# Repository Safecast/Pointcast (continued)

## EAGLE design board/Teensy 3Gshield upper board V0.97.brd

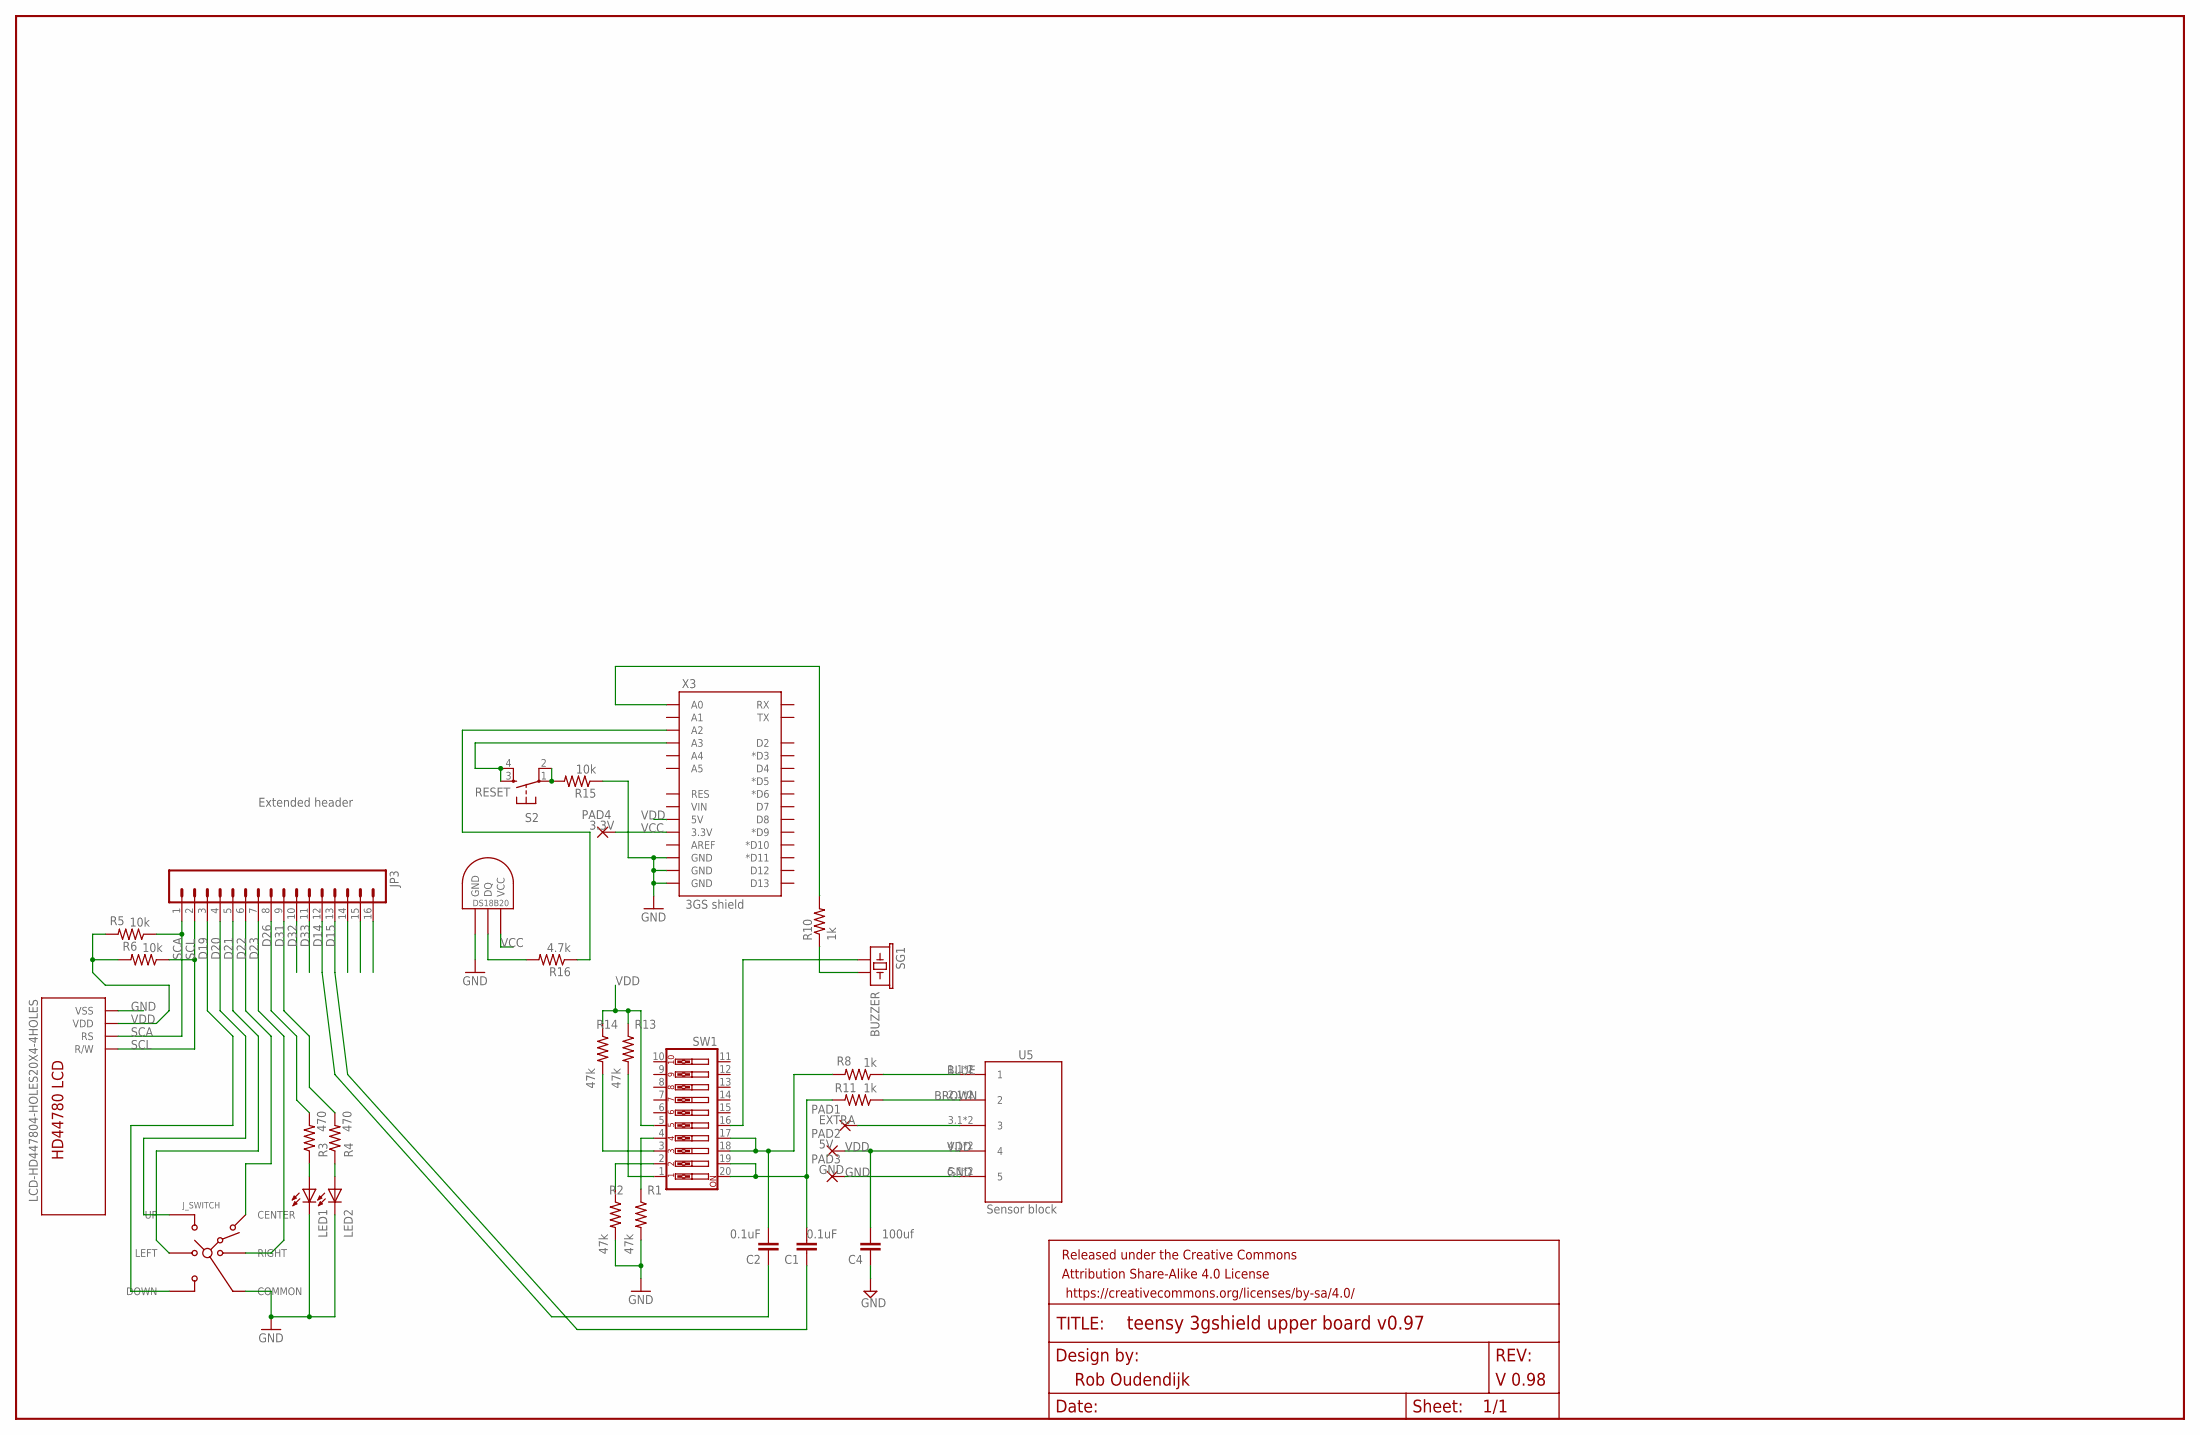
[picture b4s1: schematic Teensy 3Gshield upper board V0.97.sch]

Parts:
C1, C2: 0.1uF; CAP-PTH-SMALL-KIT
C4: 100uf; C025-024X044
FRAME1: FRAME-LEDGER; CREATIVE_COMMONS
JP3: Extended header; 1X16
J_SWITCH: SKQUCAA010; SKQU
LED1, LED2: LED5MM
PAD1: EXTRA; 2,15/1,0
PAD2: 5V; 2,15/1,0
PAD3: GND; 2,15/1,0
PAD4: 3.3V; 2,15/1,0
R1, R2, R13, R14: 47k; AXIAL-0.3
R3, R4: 470; AXIAL-0.3EZ
R5, R6: 10k; AXIAL-0.3
R8, R11: 1k; AXIAL-0.3
R10: 1k; AXIAL-0.3EZ
R15: 10k; AXIAL-0.3EZ
R16: 4.7k; AXIAL-0.3EZ
S2: RESET; DTS-6
SG1: BUZZER; BUZZER-12MM
SW1: SW_DIP-10; EDG-10
U5: Sensor block; SREWLESS_TERMINATOR_5PIN
U$2: DS1820TO92; DS1820
X1: LCD-HD447804-HOLES20X4-4HOLES; LCD-20X4-4HOLES
X3: 3GS shield; DUEMILANOVE_SHIELD

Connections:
BLUE: R8.P$1 (1), U5.1.1 (1), U5.1.2 (1)
BROWN: R11.P$1 (1), U5.2.1 (2), U5.2.2 (2)
D14: JP3.12
D15: JP3.13
D19: JP3.3, J_SWITCH.DOWN
D20: JP3.4, J_SWITCH.UP
D21: JP3.5, J_SWITCH.LEFT
D22: JP3.6, J_SWITCH.CENTER
D23: JP3.7, J_SWITCH.RIGHT
D26: JP3.8, R3.P$2 (2)
D31: JP3.9, R4.P$2 (2)
D32: JP3.10
D33: JP3.11
GND: C4.1, J_SWITCH.COMMON, LED1.K (C), LED2.K (C), PAD3.1, R1.P$2 (2), R2.P$2 (2), R15.P$1 (1), U5.5.1 (5), U5.5.2 (5), U$2.GND, X1.P$13 (VSS), X3.GND@0 (GND), X3.GND@1 (GND), X3.GND@2 (GND)
unnamed: SG1.+ (1), SW1.16
unnamed: LED1.A, R3.P$1 (1)
unnamed: R10.P$2 (2), X3.A0
unnamed: R14.P$2 (2), SW1.3
unnamed: R10.P$1 (1), SG1.- (2)
unnamed: R16.P$2 (2), U$2.DQ
unnamed: C1.2, R11.P$2 (2), SW1.19, SW1.20
unnamed: R16.P$1 (1), X3.A2
unnamed: R13.P$2 (2), SW1.1
unnamed: LED2.A, R4.P$1 (1)
unnamed: R15.P$2 (2), S2.1, S2.2
unnamed: S2.3, S2.4, X3.A3
unnamed: C2.2, R8.P$2 (2), SW1.17, SW1.18
unnamed: PAD1.1, U5.3.1 (3), U5.3.2 (3)
SCA: JP3.1, R5.P$1 (1), X1.P$15 (RS)
SCL: JP3.2, R6.P$1 (1), X1.P$16 (R/W)
VCC: PAD4.1, U$2.VDD (VCC), X3.3.3V
VDD: C4.2, PAD2.1, R5.P$2 (2), R6.P$2 (2), R13.P$1 (1), R14.P$1 (1), SW1.5, U5.4.1 (4), U5.4.2 (4), X1.P$14 (VDD), X3.5V
VDD1: R1.P$1 (1), R2.P$1 (1), SW1.2, SW1.4

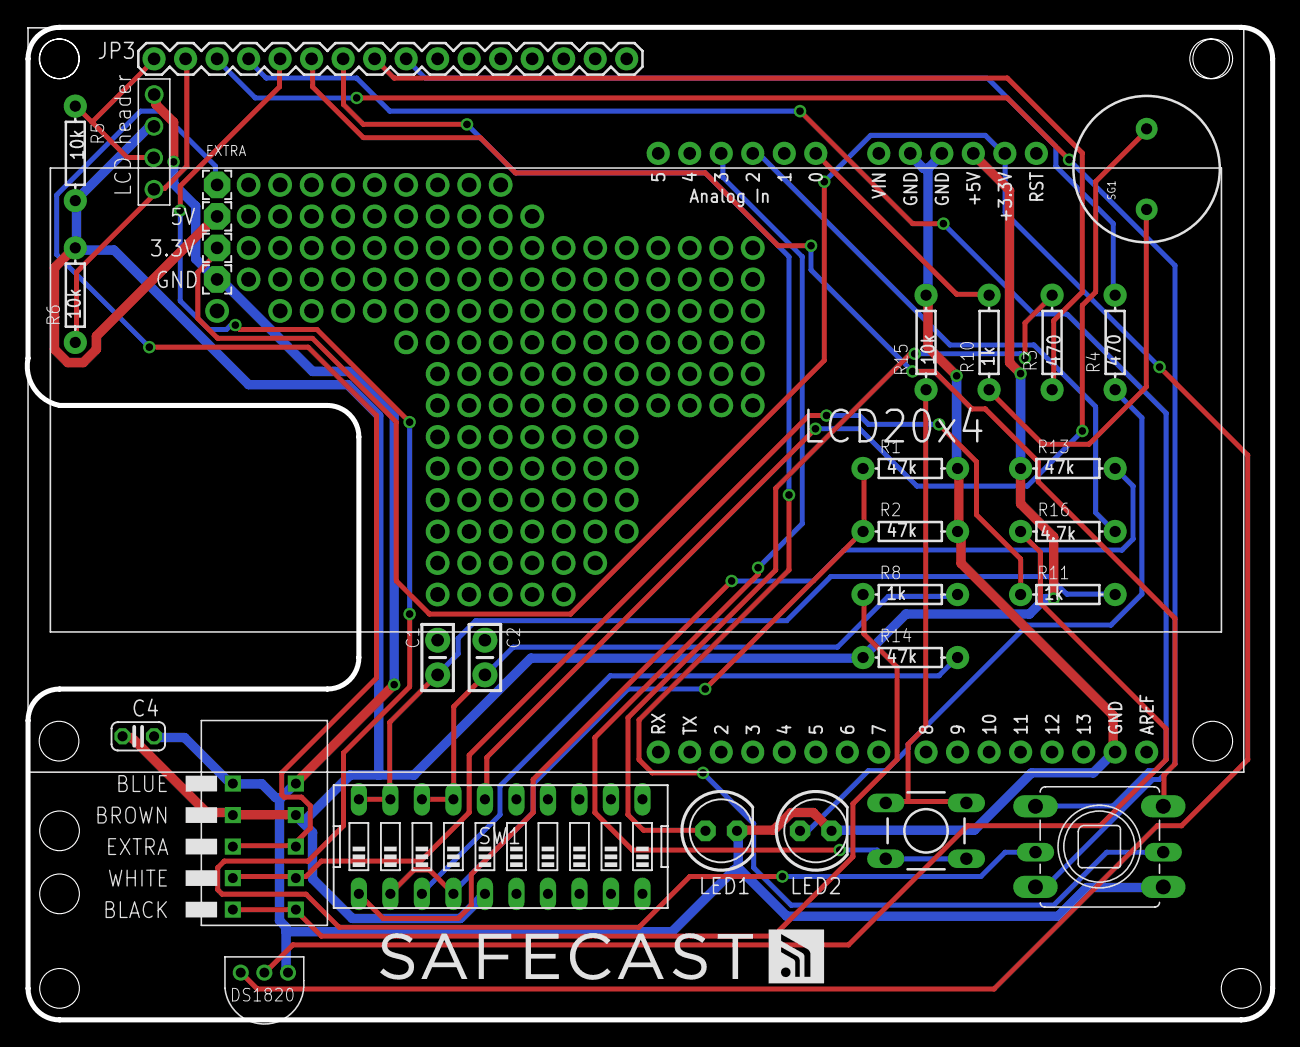
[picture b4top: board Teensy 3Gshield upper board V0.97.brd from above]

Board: 2 copper layers, 100.4 x 80.0 mm, 33 parts (0 on the bottom side), 29 nets.

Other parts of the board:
U$10: SAFECAST_LOGO1

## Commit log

2015-02-28 initial project version
2015-03-03 Fixed dual upload and interupt routine deleted displaying pulses.
2015-03-03 Added zipped hex file
2015-03-03 Changed time for sending to 5 minutes.
2015-03-03 Version change
2015-03-03 And the compressed hex file
2015-03-03 Changed display messages
2015-03-03 layout of display changed
2015-03-05 Pull up active on inputs inputs are setup for falling edge
2015-03-07 Added upldated Hex file
2015-03-07 renamed Hex zip file
2015-03-09 Added libraries and new boards
2015-03-09 Added more files
2015-03-09 Update I2C library and added Hex file
2015-03-09 Added Gerber files
2015-03-09 Cleaned up code, added final boards.
2015-04-01 Create gh-pages branch via GitHub
2015-04-04 Added reset to A14
2015-04-05 Added LED check on startup..
2015-04-06 LED delay setup
2015-04-07 Code for Ethetnet and 3G combined
2015-04-07 Send and recieve every 5 minutes. (2.6.1 was every 5 seconds for stress testing)
2015-04-09 Switch between DEV and API sending the data...
2015-04-13 added switch for switching from Ethernet and other options to switch in the coding without recompile.
2015-04-13 Added heart beat on green LED every 10 seconds..
2015-04-14 Switched back to two compile versions(3G and Ethernet) and added setup variables
2015-04-14 Added extra setup files
2015-04-21 V2.6.8 added device ID, startup screen change, header for file format changed to NGRDD
2015-04-23 Sensor header added as second line on SDcard
2015-04-27 Changed name repro
2015-04-27 changed name
2015-04-27 And all the other files updated to Pointcast
2015-04-27 More files
2015-04-27 Version named too..
2015-04-27 Added latest boards
2015-04-27 And the boards
2015-04-30 Added temperature setup for DS18B20 (disabled at the moment) setup screens
2015-05-02 V2.7.3 Added joystick setup functions, cleanup code
2015-05-04 Added height info
2015-05-04 Fixed lot/lan sending information on Ethernet
2015-05-07 V2.7.3 with SDCard files corrected..
2015-05-07 Display SDCard errors was disabled.. Now enbaled.
2015-05-08 V2.7.4 More screens and error reporting.
2015-05-10 Renaming and 3G display screen setup
2015-05-10 Added sdcard files
2015-05-14 BOM updated
2015-05-16 V2.7.9 Added Joystick interaction. Key down startup 1/5 of normal time. Prepare joy stick enter ket (push down) for other functions.
2015-05-16 Extra files added
2015-05-18 Automatic time setup on Ethernet NTP
2015-05-19 Fixes for 3G after RTC updates (RTC for 3G not setup yet)
2015-05-20 Added random auto gateway , added fast troubleshooting mode
2015-05-22 Added "trb=0" option to the sdcard setup be able to fast trouble shoot the senor
2015-05-24 Modified 3GIM library for faster access.
2015-05-24 And the files
2015-05-24 Added the missing version number
2015-05-31 Interactive menu fixes.
2015-06-05 V2.9.1. updated for loud buzzer and fast sensing setup select from SDcard
2015-06-07 Temperature setup, APIKEY display, battery/power updated
2015-06-07 Added .gitignore
2015-06-09 Temperature fix and some display changes.
2015-06-17 Fixes for sdcard temp and battery, file naming, etc
2015-06-20 V2.9.8 Switch between API and DEV by sdcard setting (dev=1 for sending data to dev.safecast.org)
2015-06-22 V2.9.9 DEV status on LCD
2015-06-22 V3.0.0 Fix second line
2015-06-27 V3.0.2 Height added
2015-07-01 V3.0.4 fixed for diagnostics/RTC and network setup
2015-08-15 V3.07 fixed dsiplay bug for Ethernet
2015-08-18 Changed voltage display to compansate for voltage drop over D103
2015-08-20 Switched Teensy to intrenal reference mode 1.2V
2015-08-25 Ethernet MAC setup from SDCARD
2015-08-25 Imporved SD card fail logic
2015-08-25 Added Carrier display for 3G and change voltage display with no diode compensation
2015-08-25 Modified Mac display to be always how two digits
2015-09-02 Add libs
2015-09-02 And the rest of the files
2015-09-03 Added missing libs
2015-09-06 V3.2.4 misc fixes
2015-09-11 V3.2.5 changed FAILS display in 3G and Ethernet
2015-09-18 Added documentions
2015-09-19 V3.2.8 Added single sensor not faling on test
2015-09-28 Weekly reset setup
2015-09-28 Added correct version number
2015-10-03 Weekly reset and 3 beeps before restart. On boot two beeps
2015-10-22 Misc fixes V3.3.2
2015-11-12 Changed the way 3G connects to APN
2015-11-16 V3.3.5 Eeprom cleared on pressing enter key of Joystick at start menu.
2015-11-17 V3.3.6 added reset failure LED by enter (push down) joyswitch
2015-11-19 More fixes display
2015-12-11 V3.4.0 EEprom storage
2015-12-16 3G connect fail error display fixes.
2016-01-01 V3.4.2 Fixed Ethernet display
2016-01-05 Change network parameters for 3G
2016-01-18 Added massages for connect with httpPOST 3G
2016-01-24 Added extra code for different temperature sensors.
2016-01-26 Changed way to send data for 3G ..powerup-send-powerdown...
2016-02-01 Setup alarm
2016-02-15 Added retries 3 time to 3G and hard reset.
2016-02-18 Added reply messages for API to display on treminal screen.
2016-02-19 Cleaned up formatting
2016-02-20 Fixes for Ethernet time issues and time sending to API
2016-02-21 Fixes for timezone and lockups
2016-03-02 V3.6.0 fixed Ethernet not connected
2016-03-05 Fixes for timestaming.
2016-03-06 Daily restarts
2016-03-06 V3.6.5 Fixed another time bug.
2016-03-08 V3.6.6 Cleaned out debug code
2016-03-09 V 3.6.7 Added test for pinging network in Ethernet and 3G mode in startup
2016-03-10 V3.6.8 added ping menus, RTC menu and build logic for menu
2016-03-11 V3.6.8 implemented ping menu, added documentation
2016-03-11 Added extra docs.
2016-03-11 More docs.
2016-03-11 V3.7.0 ping tests for 3G and Ethernet setup.
2016-03-13 V3.7.1 redone screenflow
2016-03-13 V3.7.1 GW02/GW02 setup -ping Google.com
2016-03-14 V3.7.4 display time remaing to sent and ping setup to s3
2016-03-17 V3.7.7 create log entries are stored in EEProm
2016-03-27 V3.7.8 added temperature on main screen, dev and api switch on display, logging header with logs, retarts and fails
2016-03-28 V3.7.9 Fixed after EEprom errase no counting error.
2016-03-31 Pointcast for Hosting People JP.pdf
2016-04-17 Use push key to stop display screen for 100 seconds
2016-04-19 V3.8.2 Added pause at screens.
2016-04-22 V 3.8.3 Fix for starting at always on 5 minutes count down.
2016-04-27 V3.8.4 disbaled adaptive counting
2016-04-29 V3.8.6 added phone number setup from sdcard for 3G, changed display data to 1 minute, changed NX to 12 and delay to 5000 for 5 seconds measuring, KCPM 2 charater after decimal point
2016-04-29 V3.8.7 added \n to new log file to keep data separated from comment.
2016-05-05 V3.8.8 display silding window data every 5 minutes only
2016-05-05 Added Kicad files for V1.03 board
2016-05-15 V3.8.9 DNS setup for NTP timeserver (before hardcoded to pool.ntp.org)
2016-05-15 V3.9.0 Xbee setup
2016-05-21 V3.9.1 Menu fixed in 3G and Ethernet.
2016-06-09 V3.9.2 Added FreeRam on display, serial out and on sdcard.
2016-06-17 V3.9.4 Cocde clean and 5 minutes count from all bins.
2016-07-07 V3.9.5 Ethernet reset before startup.
2016-07-08 V3.9.6 Weekly reset init moved after TeensClock is set.
2016-07-12 V3.9.6 Ethernet hex file
2016-07-12 V3.9.6 3G hex file
2016-07-16 V3.9.7 Added interruptCounterReset() just before count starts
2016-07-21 V3.9.8 true random minutes at weekly restarts.
2016-07-22 V3.9.8 3G fixed weekly restats to be randowm within one hour
2016-07-27 V3.9.9 fixed for DS18S20 sensor.
2016-07-27 V4.0.0 adjusted display for ethernet and 3G to display count down in 4 digits and get even spaces for the voltage and temperature.
2016-07-29 V4.0.2 Misc 3G and Ethernet connection changes
2016-08-01 V4.0.3 improved weekly restart based on rst value on sdcard
2016-08-01 Added link update firmware
2016-08-03 Added Hex files
2016-08-03 Added files
2016-08-10 V4.0.5 moved 3GIM powerdown/up closer to startup to give 3GIM module more time settle down before startup
2016-08-28 Added holes for glands placement for Ethernet
2016-08-28 Updated holes pictures
2016-08-29 V4.0.6 fixes Ethernet S1 LED problem.
2016-09-09 V4.0.7 fixed retries Ethernet
2016-09-09 V4.0.8 added 3 seconds delay between retries Ethernet
2016-09-15 V4.0.9 fixes for NTP server (Ray suggestions)
2016-09-17 V4.1.1 weekly reset redone, failure messages on SDcard, misc fixes
2016-09-18 V4.1.2 many warnings from compiler fixes.
2016-09-18 V4.1.3 NTP timeout of retries to server 5 minutes.
2016-09-20 V4.1.4 Fixed temp sensor
2016-09-22 V4.1.5 clened up formating
2016-09-22 V4.1.6 setup NTP check for 15 seconds retries and 300 seconds timeout
2016-09-23 V4.1.7 setup to renew a lease for DHCP every 5 minutes for networks that have short DHCP lease setup
2016-10-07 Added app folder for Mac uploader app with newest firmware for 3G and Ethernet
2016-10-07 Zipped the apps for easy downlaoding from github.
2016-10-07 And added the zips.
2016-10-17 V4.1.9 addded confirmation of measurement_id recieved by API.
2016-10-27 V4.2.0 Added status reporting to API.
2016-10-27 V4.2.1 Fix for Ethernet Status sending
2016-10-29 V4.2.2 display measurements_id in terminal display in Ethernet mode
2016-10-31 V4.2.3 Fixed 3G for send display
2016-11-05 V4.2.3 with hex and app files added.
2016-11-08 Added correct drill template box and sdcard configs zipped
2016-11-13 V4.2.4 3G error messages on fail fix.
2016-11-21 Added teensy.exe for windows teensy flashing
2016-11-21 Change the Teensy.exe for zipped version
2016-11-25 Added docs for updating firmware for windows in english and japanese.
2016-12-10 Updated hole placement for case.
2017-02-13 V4.2.5 SDcard edit with Windows text edittor fix.
2018-05-16 test
2018-05-16 removed test
2018-06-02 Fixed reading cr/lf for sdcard reading (honor goes to Ray)
2018-06-02 Added version update
2018-09-05 test for Ethernet 2 version
2018-09-05 Added correct libraries
2018-09-05 Added more libraries
